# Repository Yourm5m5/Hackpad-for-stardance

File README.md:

# Hackpad — 3-Key Media Macropad

Hackpad is an ultra-compact, custom-built 3-key mechanical macropad powered by the **Seeed Studio XIAO RP2040** and running **KMK Firmware**. It features custom Tap Dance functionality, allowing you to seamlessly control volume, track navigation, and media playback with only three physical switches.

---

## Features

* **Compact Form Factor:** Designed around the tiny Seeed XIAO RP2040 footprint.
* **Tap Dance Controls:** Get 6 different media functions out of just 3 physical keys.
* **Premium Build Hardware:** Uses durable M3 heatset inserts for a robust, reusable 3D-printed case assembly.
* **Custom PCB Design:** Clean, reliable hardware routing (no messy hand-wiring birds-nests!).

---

## Design & Gallery

### Render of Macropad

### 3D Model of Case

### PCB Layout

### Schematic Diagram

---

## Bill of Materials (BOM)

| Component | Description | Estimated Price (AUD) | Link |
| :--- | :--- | :---: | :--- |
| **Microcontroller** | Seeed XIAO RP2040 Development Board | ~$16.00 | [Aliexpress](https://www.aliexpress.com/item/1005007427287029.html) |
| **Switches** | MX-style mechanical switches (Linear/Tactile) | ~$11.00 | [Aliexpress](https://www.aliexpress.com/item/1005008904106530.html) |
| **Keycaps** | Blank DSA Profile PBT Keycaps | ~$5.00 | [Aliexpress](https://www.aliexpress.com/item/1005002976015114.html) |
| **Screws** | M3 × 16mm socket head screws | ~$9.00 | [Aliexpress](https://www.aliexpress.com/item/1005005041733771.html) |
| **Threaded Inserts**| M3 × 5mm (OD) × 4mm (L) brass heatset inserts | ~$5.00 | [Aliexpress](https://www.aliexpress.com/item/1005004701945081.html) |

---

## Default Keymap Layout (Tap Dance)

Thanks to KMK's `TapDance` module, every switch has two distinct functions based on how many times you press it:

| Switch | Single Tap Action | Double Tap Action |
| :---: | :--- | :--- |
| **Key 1** | 🔇 Mute / Unmute | Play / Pause Video |
| **Key 2** | 🔊 Volume UP | kip Forward (Next Track) |
| **Key 3** | 🔉 Volume DOWN |  Skip Backward (Previous Track) |

---

## Software & Firmware Setup

The Hackpad runs on **CircuitPython** paired with the **KMK Keyboard Firmware framework**. 

### 1. Flash CircuitPython
1. Download the latest `.uf2` stable firmware for the **Seeed XIAO RP2040** from [circuitpython.org](https://circuitpython.org/downloads).
2. Connect your XIAO to your computer while holding down the **BOOT** button.
3. A new flash drive named `RPI-RP2` will appear. Drag and drop the downloaded `.uf2` file onto it.
4. The board will reboot automatically as a USB drive named **`CIRCUITPY`**.

### 2. Install KMK Library
1. Download the KMK Firmware source code from the official [KMK GitHub Repository](https://github.com/KMKfw/kmk_firmware).
2. Copy the folder named `kmk` from the ZIP directly onto your `CIRCUITPY` drive root.

### 3. Add the Configuration Script
Save the following production code to your `CIRCUITPY` drive as **`code.py`**:

```python
import board
from kmk.kmk_keyboard import KMKKeyboard
from kmk.keys import KC
from kmk.scanners import DiodeOrientation
from kmk.extensions.media_keys import MediaKeys
from kmk.modules.tapdance import TapDance

keyboard = KMKKeyboard()

# Enable media controls and Tap Dance features
keyboard.extensions.append(MediaKeys())
tapdance = TapDance()
tapdance.tap_time = 250  # Double-tap window in milliseconds
keyboard.modules.append(tapdance)

# Matrix hardware layout pins for Hackpad
keyboard.col_pins = (board.D9,)
keyboard.row_pins = (board.D10, board.D11)
keyboard.diode_orientation = DiodeOrientation.COL2ROW

# Configure Tap Dance Macros (Single Tap, Double Tap)
MUTE_PAUSE = KC.TD(KC.AUDIO_MUTE, KC.MEDIA_PLAY_PAUSE)
VOL_UP_FORWARD = KC.TD(KC.AUDIO_VOL_UP, KC.MEDIA_NEXT_TRACK)
VOL_DOWN_BACK = KC.TD(KC.AUDIO_VOL_DOWN, KC.MEDIA_PREV_TRACK)

# Apply configuration to keys mapping
keyboard.keymap = [
    [
        MUTE_PAUSE,       # Key 1
        VOL_UP_FORWARD,   # Key 2
        VOL_DOWN_BACK     # Key 3
    ]
]

if __name__ == "__main__":
    keyboard.go()
```

## Credits
I use AI to help me structure my repo

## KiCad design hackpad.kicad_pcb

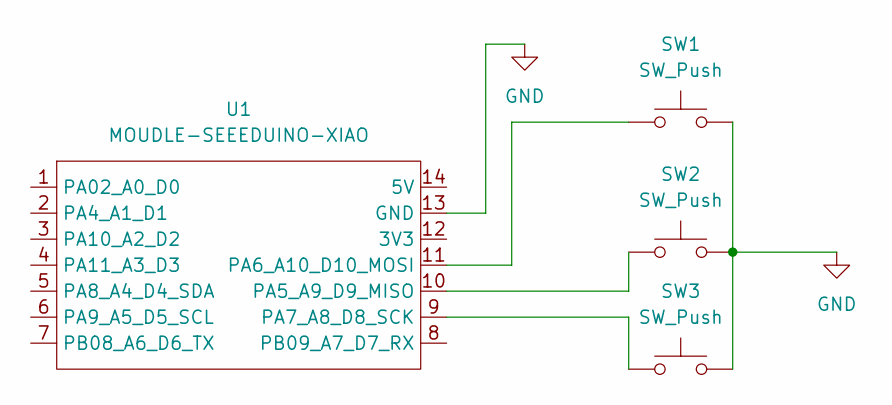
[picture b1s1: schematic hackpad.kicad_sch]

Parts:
SW1, SW2, SW3: SW_Push; SW_Cherry_MX_1.00u_PCB
U1: MOUDLE-SEEEDUINO-XIAO; XIAO-Generic-Hybrid-14P-2.54-21X17.8MM

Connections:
GND: SW1.2, SW2.2, SW3.2, U1.13 (GND)
unnamed: SW2.1, U1.10 (PA5_A9_D9_MISO)
unnamed: SW1.1, U1.11 (PA6_A10_D10_MOSI)
unnamed: SW3.1, U1.9 (PA7_A8_D8_SCK)

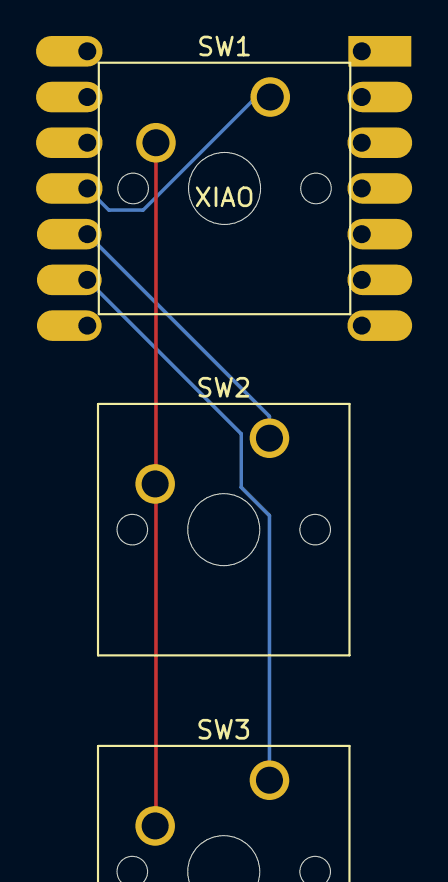
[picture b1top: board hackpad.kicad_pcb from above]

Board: 2 copper layers, 4 parts (1 on the bottom side), 4 nets.
